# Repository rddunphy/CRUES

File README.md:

# CRUES
Co-operative robotics using environmental sensors

## Directory structure

* `docs`: Documentation, including PDF of final report
  * `docs/interim`: Interim report LaTeX root
  * `docs/final`: Final report LaTeX root
  * `docs/img`: Image root for reports
* `wiring`: Wiring diagrams, PCB files
* `rviz`: Rviz configuration files for visualising odemetry and mapping data
* `crues_pi`: ROS nodes and Python code
  * `crues_pi/ros_pkgs`: ROS packages to be added to catkin workspace
  * `crues_pi/crues`: Scripts used for testing and debugging
  * `crues_pi/config`: Configuration files for individual robots
       (Deploy script copies correct file to each RPi)
  * `crues_pi/crues_deploy`: Script for deploying code to RPis
  * `crues_pi/crues_run`: Script for running Roomba code on RPis

## Deploying and running code

* Turn on robots
* Connect to `CruesNet` ad-hoc WiFi network
* Add `crues_pi/crues_deploy` and `crues_pi/crues_run` to PATH
* Run `crues_deploy [ROBOTS]` to deploy code, with `[ROBOTS]` replaced by any combination of `blinky`, `inky` and `clyde`
* Run `crues_run [ROBOTS]` to run the `roomba.launch` ROS launch file

More details can be found in the [project Wiki](https://github.com/rddunphy/CRUES/wiki).

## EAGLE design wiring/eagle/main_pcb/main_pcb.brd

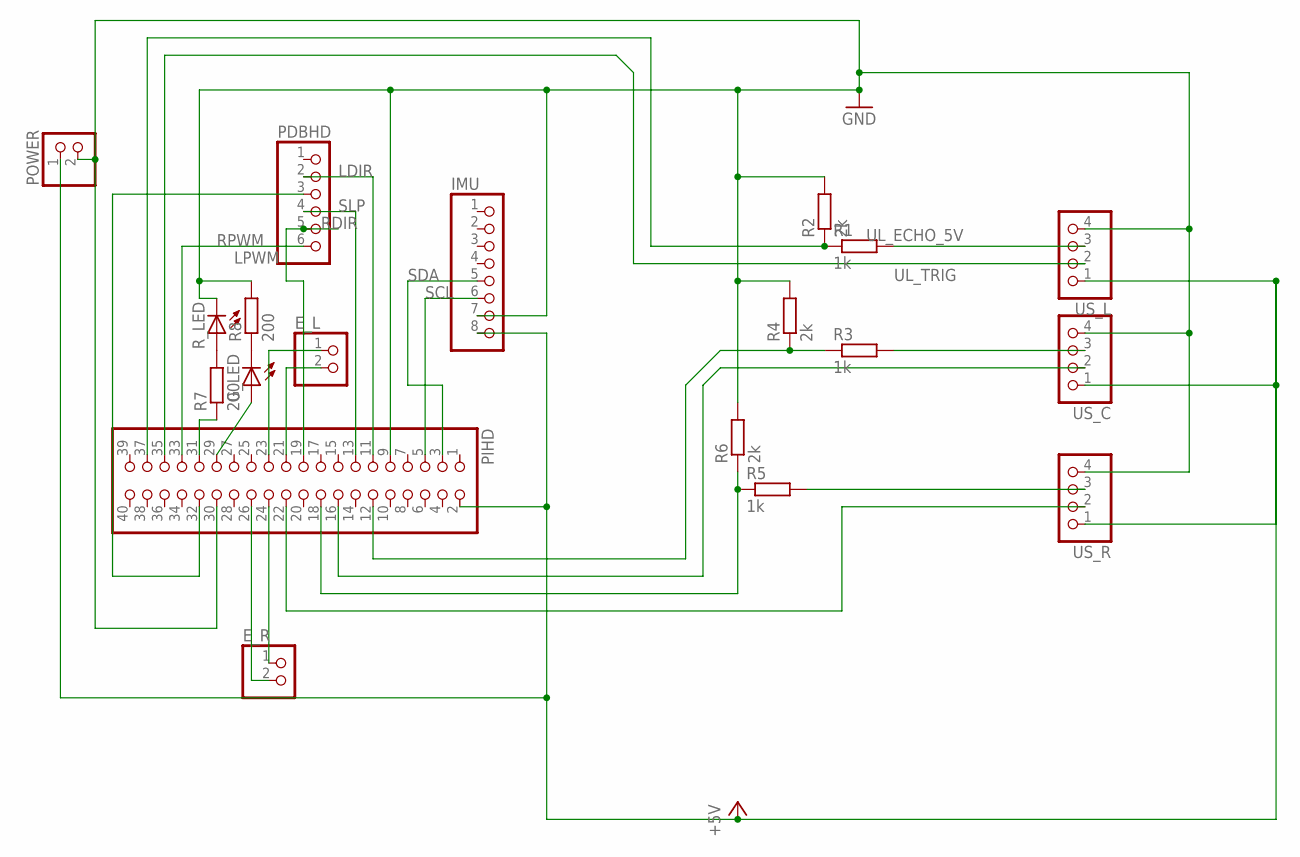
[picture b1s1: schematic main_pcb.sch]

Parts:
E_L: PINHD-1X2; 1X02
E_R: PINHD-1X2; 1X02
G_LED: LED_ELD260; LED_LD260
IMU: PINHD-1X8; 1X08
PDBHD: PINHD-1X6; 1X06
PIHD: PINHD-2X20; 2X20
POWER: PINHD-1X2; 1X02
R1, R3, R5: 1k; 0207/10
R2, R4, R6: 2k; 0207/10
R7, R8: 200; 0207/10
R_LED: LED_ELD260; LED_LD260
US_C: PINHD-1X4; 1X04
US_L: PINHD-1X4; 1X04
US_R: PINHD-1X4; 1X04

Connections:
+5V: IMU.8, PIHD.2, POWER.1, US_C.1, US_L.1, US_R.1
ER_A: E_R.1, PIHD.24
ER_B: E_R.2, PIHD.26
GND: IMU.7, PIHD.9, PIHD.30, POWER.2, R2.2, R4.2, R6.2, R8.2, R_LED.K (C), US_C.4, US_L.4, US_R.4
LDIR: PDBHD.2, PIHD.11
LED_G: G_LED.A, PIHD.29
LED_R: PIHD.31, R7.1
LPWM: PDBHD.3, PIHD.32
unnamed: E_L.2, PIHD.21
unnamed: E_L.1, PIHD.23
unnamed: R7.2, R_LED.A
unnamed: G_LED.K (C), R8.1
RDIR: PDBHD.5, PIHD.19
RPWM: PDBHD.6, PIHD.33
SCL: IMU.6, PIHD.5
SDA: IMU.5, PIHD.3
SLP: PDBHD.4, PIHD.13
UC_ECHO: PIHD.12, R3.1, R4.1
UC_ECHO_5V: R3.2, US_C.3
UC_TRIG: PIHD.16, US_C.2
UL_ECHO: PIHD.37, R1.1, R2.1
UL_ECHO_5V: R1.2, US_L.3
UL_TRIG: PIHD.35, US_L.2
UR_ECHO: PIHD.18, R5.1, R6.1
UR_ECHO_5V: R5.2, US_R.3
UR_TRIG: PIHD.22, US_R.2

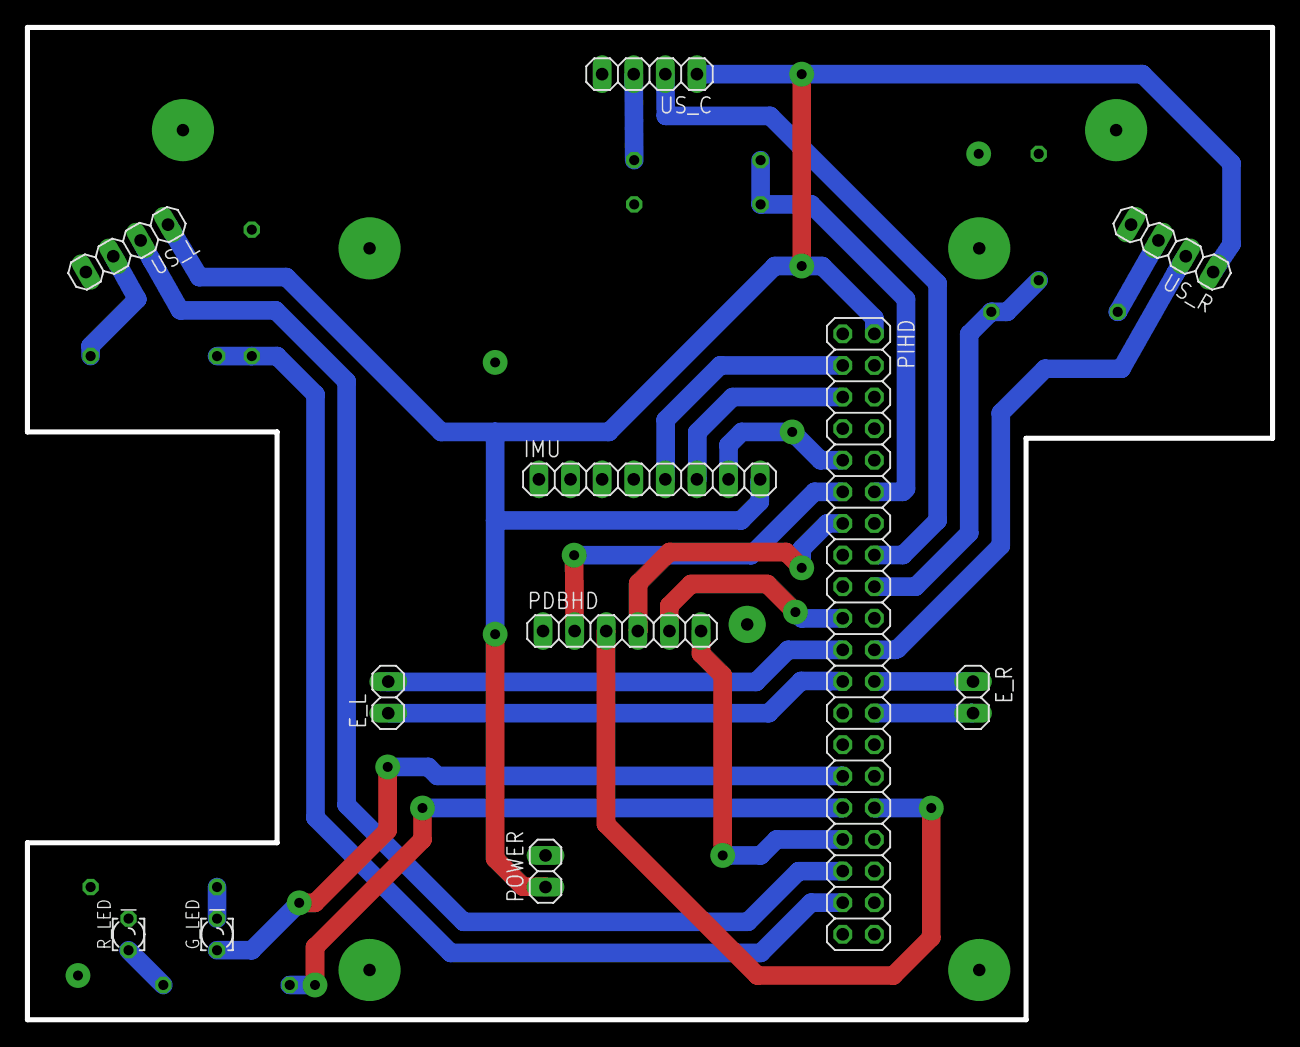
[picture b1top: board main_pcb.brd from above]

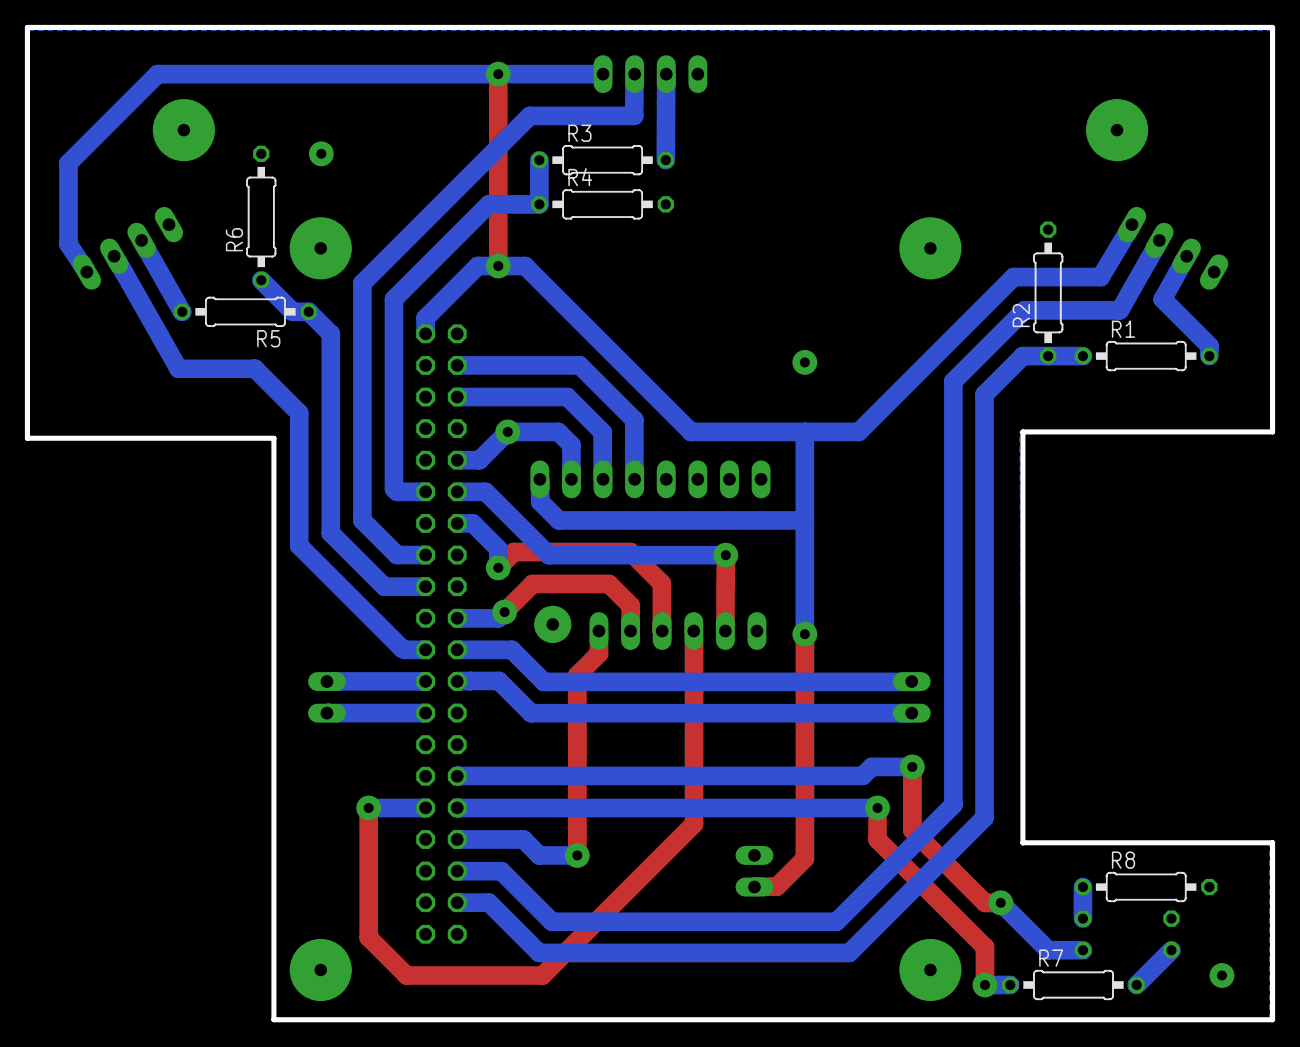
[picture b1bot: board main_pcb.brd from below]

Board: 2 copper layers, 100.1 x 79.8 mm, 19 parts (8 on the bottom side), 26 nets.

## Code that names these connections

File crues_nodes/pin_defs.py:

#!/usr/bin/env python3
"""Pin definitions for Raspberry Pi GPIO."""

# Ultrasonic sensors
UL_TRIG = 38
UL_ECHO = 40
UC_TRIG = 37
UC_ECHO = 35
UR_TRIG = 31
UR_ECHO = 29

# IMU serial pins
IMU_SCL = 5
IMU_SDA = 3

# Encoder outputs
EL_A = 22
EL_B = 18
ER_A = 13
ER_B = 11

# Motor control pins
ML_DIR = 12
ML_PWM = 32
MR_DIR = 7
MR_PWM = 33
M_SLP = 16

# LED indicators
LED_RED = 36
LED_GREEN = 28


def print_config():
    print("Ultrasonic")
    print("UL_TRIG: {}".format(UL_TRIG))
    print("UL_ECHO: {}".format(UL_ECHO))
    print("UC_TRIG: {}".format(UC_TRIG))
    print("UC_ECHO: {}".format(UC_ECHO))
    print("UR_TRIG: {}".format(UR_TRIG))
    print("UR_ECHO: {}".format(UR_ECHO))
    print()
    print("IMU")
    print("IMU_SCL: {}".format(IMU_SCL))
    print("IMU_SDA: {}".format(IMU_SDA))
    print()
    print("Encoders")
    print("EL_A: {}".format(EL_A))
    print("EL_B: {}".format(EL_B))
    print("ER_A: {}".format(ER_A))
    print("ER_B: {}".format(ER_B))
    print()
    print("Motor control")
    print("ML_DIR: {}".format(ML_DIR))
    print("ML_PWM: {}".format(ML_PWM))
    print("MR_DIR: {}".format(MR_DIR))
    print("MR_PWM: {}".format(MR_PWM))
    print("M_SLP: {}".format(M_SLP))
    print()
    print("LEDs")
    print("LED_RED: {}".format(LED_RED))
    print("LED_GREEN: {}".format(LED_GREEN))


if __name__ == '__main__':
    print_config()

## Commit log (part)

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2019-03-31 Fix concurrent.futures requirement
2019-03-31 Refactor encoder node as class
2019-03-31 Refactor ultrasonic node as class.
2019-03-31 proof reading
2019-04-01 Matt report (#39)
    * Saving files before refreshing line endings
    * git ignore upddate
    * i forget but its hoometime
    * more electrical stuff
    * added listing to imports, electrical stuff minor change in 4
    * ultrasonic software and some error fixing
2019-04-01 Kyle report (#43)
    * kfj
    * Proof read slam and updated
    * Added docs/images from abstract, group overview and posters
2019-04-01 Peter report (#45)
    * Attempt to commit docs changes
    * Refactored final doc
    * Project management report stuff
    * A little bit of pm
    * Mech doc
    * Add gitattributes file to protect against windows line endings
2019-04-01 Fetch rosbag files in deploy script.
2019-04-01 added vision in
2019-04-01 dleeted drive node
2019-04-01 Fix timezone problem
2019-04-01 No significant changes
2019-04-01 Update CMakeLists.txt
    Remove merge conflict
2019-04-01 Chassis mech changes
2019-04-01 Add IMU to robot.launch
2019-04-01 Make deploy script compatible with Andrew's weird laptop
2019-04-01 rossed the vision
2019-04-01 Consultations
2019-04-01 Gantt chart changes
2019-04-01 added code to read picam
2019-04-01 Matt report (#59)
    * Saving files before refreshing line endings
    * git ignore upddate
    * i forget but its hoometime
    * more electrical stuff
    * added listing to imports, electrical stuff minor change in 4
    * ultrasonic software and some error fixing
2019-04-01 Add rviz config file
2019-04-01 Minor fixes for EKF - main part still doesn't work
2019-04-01 Don't add Rosbag output files
2019-04-01 added pcb pic
2019-04-01 Report matt (#74)
    * added vision in
    * dleeted drive node
    * rossed the vision
    * Altered vision_node.py and package structure to allow building and running, still doesn't work
    * added code to read picam
    * tidied electronics section
2019-04-02 Add null launcher, which launches a control node that does nothing.
2019-04-02 Rename some topics for consistency, and disable IMU EKF node, as this seems to mess things up.
2019-04-02 Update topic names in rviz config
2019-04-02 Wrote the ROS background section with added references
2019-04-02 Kyle report (#75)
    * kfj
    * Proof read slam and updated
    * Added docs/images from abstract, group overview and posters
    * LE
    * Wrote the ROS background section with added references
2019-04-02 Added shortest path stuff
2019-04-02 PM section ready for review
2019-04-02 Fixed bugs and found Blinky
2019-04-02 Removed rosbag files
2019-04-02 Added up to date comms?
2019-04-02 AI and Rate control
2019-04-02 Check if robot is in view before sending
2019-04-02 Make server node class
2019-04-03 Here we go
2019-04-03 Add rospy rate to client
2019-04-03 First time, every time
2019-04-03 Made us_node more threaded
2019-04-03 Removed transform from diff_tf
2019-04-03 Add polygon controller that tries to go in a rectangle, and startup delay to avoid odometry offset.
2019-04-03 Minor changes
2019-04-03 Minor changes based on Peter's feedback
2019-04-03 Remove the excess PID stuff that came in from a previous merge
2019-04-03 Dumped US output to usdumps file
2019-04-03 Pete might be an idiot
2019-04-03 Calculated averages and put in output.txt
2019-04-03 Add Gmapping and LaserScan message
2019-04-04 Review of Project Management
2019-04-04 Need the EKF because that broadcasts the odom->baselink tf
2019-04-04 Add SLAM parameters
2019-04-04 Add screenshots
2019-04-05 Add ultrasonic diagram
2019-04-05 added recording functionality
2019-04-05 Remove accidental spacing
2019-04-05 Add path controller
2019-04-05 video improvements
2019-04-05 Start on software comms
2019-04-05 Software changes
2019-04-05 Finished Comms Design
2019-04-06 backround review
2019-04-06 More testing
2019-04-06 Testing with new lines this time
2019-04-06 Forgot to build
2019-04-06 General eval section started?
2019-04-06 Ignore rosbag directory in Git
2019-04-06 Create graph of ultrasonic response
2019-04-06 Add response to ultrasonic code
2019-04-06 Export graphs as images
2019-04-06 Add commands for setting velocity, pausing, and exiting to path controller
2019-04-06 More comms software
2019-04-06 File paths are case-sensitive
2019-04-07 Added Comms testing
2019-04-07 Start work on implementation section
2019-04-08 changes from 5/4
2019-04-08 Added changes based on Matt's susggestions
2019-04-08 Updated background for lines and other stuff
2019-04-08 Apply suggestions from code review
2019-04-08 Computer vision draft
2019-04-08 Computer vision added goal
2019-04-08 More eval
2019-04-08 Fix online references
2019-04-08 Python version subsection
2019-04-08 Minor background changes
2019-04-08 Changed paragraphs to lines
2019-04-08 Changes from Andrew's feedback
2019-04-08 Think it's fixed
2019-04-08 initial review
2019-04-08 Changes to parameters for Gmapping
2019-04-08 Move launch files to launch directories, and make ultrasonic return range in metres
2019-04-08 Refactor IMU node as class
2019-04-08 Don't need AI package at this rate
2019-04-08 Use robots.yaml for IP addresses
2019-04-08 Move config files to crues_control package
    Robot-specific config (e.g. pin definitions) in parameterised files in config directory - the correct file is selected by deploy.sh
2019-04-08 Don't need setup script anymore
2019-04-08 Requirements might still be useful, though.
2019-04-08 Publish to motor_sleep
2019-04-09 Fix minor bugs
2019-04-09 Tweak slam parameters and ignor comments in path files
2019-04-09 Update map scanner more frequently
2019-04-09 Add pinout for inky
2019-04-10 Add IMU rosbag for IMU video creation
2019-04-10 Add rviz config for IMU output
2019-04-10 Add table of pin definitions
2019-04-10 Uh oh spaghetti os
2019-04-10 review of intro
2019-04-10 A line
2019-04-10 Pin defs for clyde
2019-04-10 Update pin def table
2019-04-11 started IMU softy stuff
2019-04-11 Skim-through for getting issues together
2019-04-11 IMU image and code
2019-04-11 Requested Changes
2019-04-11 References places
2019-04-11 typos
2019-04-11 Further work??
2019-04-11 Rqeuested changes #115
2019-04-11 review
2019-04-11 References again...
2019-04-11 remove synctex temp file
2019-04-11 added loop closure stuff
2019-04-11 Because Stephen is an idiot
2019-04-11 PId complete
2019-04-11 Initial conclusion draft
2019-04-11 added citations
2019-04-11 Table problems
2019-04-11 Small change
2019-04-11 Conclusion updates from Matt's comments
2019-04-11 Wrote draft odometry section
2019-04-11 Added to Appendix A
2019-04-11 moved odometry diagram
2019-04-11 More things
2019-04-11 Fix EKF parameters
2019-04-11 Add some ekf stuff
2019-04-11 Pin assignments
2019-04-11 Misc
2019-04-11 More misc changes
2019-04-11 Modified project structure to be more consistent with reality
2019-04-11 Reviewed PID software section
2019-04-11 References stuff
2019-04-11 fixed typos for kyle and build failures for david
2019-04-11 ahhhhhh
2019-04-11 Parameterise CV colours
2019-04-11 Exclude self from list of robots to detect
2019-04-12 Basic ultrasonic synchronisation
2019-04-12 Remove conflict
2019-04-12 Add in stuff Andrew destroyed
2019-04-12 Use \verb|...| for inline code
2019-04-12 Take out some swear words
2019-04-12 Reviewed and modified software overview section
2019-04-12 Formatting Introduction
2019-04-12 review of pcb pin assignment
2019-04-12 Changes to introduction
2019-04-12 Add paragraph about output scaling to PID section
2019-04-12 Small changes
2019-04-12 start
2019-04-12 CV Review
2019-04-12 Added maze diagrams
2019-04-12 Power distro issue, needs review
2019-04-12 Forgot to reload but fixed it
2019-04-12 This time
2019-04-12 Robotics and Coop robitcs background review
2019-04-12 Please don't hurt me kyle
2019-04-12 Minor change
2019-04-12 Moved rate control to implementation to mitigate lack of references
2019-04-12 Modified rate control and stuff
2019-04-12 Appendix review, needs removed will burst before Tuesday. Recommend Dr. R.D. Dunphy for appendectomy, Dr. A. Fagan to assist
2019-04-12 Added the maze 4 Real
2019-04-12 Reviewed section, added paragraph about integration
2019-04-12 Testing Review
2019-04-12 Fixing Peter's mistake
2019-04-12 Further further work
2019-04-12 Wrote draft acknowledgement section for everyone's review. Feel free to add anything
2019-04-12 Results and something is up
2019-04-12 Minor tweaks to roomba to make it run into walls less.
    Slower turn velocity helps when there are narrow passages (one cell wide), this could be increased again for the trade show perhaps.
2019-04-12 EKF fix
2019-04-12 Forgot to reload, trying to fix
2019-04-12 Added todo
2019-04-12 Maze configuration diagrams
2019-04-13 Read-through part 1
2019-04-13 Read-through part 2
2019-04-13 Background/Lit review overhaul
2019-04-13 abstract redraft
2019-04-13 Read-through part 3
2019-04-13 test review
2019-04-13 pin def check
2019-04-13 some minor changes
2019-04-13 Read-through part 5
2019-04-13 wrote high level overview of package, still to write tuning
2019-04-13 Evaluation review
2019-04-13 Software evaluation
2019-04-13 Read-through part 6
2019-04-13 Further work changes
2019-04-13 Read-through part 7
2019-04-13 Read-through part 8
2019-04-13 Read-through part 9. Got partway through background on second read-through
2019-04-13 added figure and some analysis
2019-04-14 Some proof reading changes for abstract, introduction and background
2019-04-14 Background proof-read
2019-04-14 Project management changes
2019-04-14 Mechanical review
2019-04-14 Move all code to local catkin workspace
2019-04-14 Add apt packages needed for installation
2019-04-14 Sofware review
2019-04-14 Don't mention the batteries!
2019-04-14 Further work
2019-04-14 Conclusions review
2019-04-14 Fix missing page numbers in toc
2019-04-14 Proofreading
2019-04-14 Significant work on ROS software section
2019-04-14 Got rid of todos
2019-04-14 "deal with" doesn't sound reporty.
2019-04-14 Fix IMU todo
2019-04-14 Add EKF graphs
2019-04-14 Fixed ALL the Latex warnings!
    Also added todo list to the start of the report, to make todos easy to
    find
2019-04-14 Add SLAM figures
2019-04-14 fixed a couple things
2019-04-14 Add AMCL diagram
2019-04-14 Fix dates in bibliography
2019-04-14 Fixed build error
2019-04-14 Changed some things in conclusion
2019-04-14 Review software intro
2019-04-15 Minor again
2019-04-15 Add all chapters to texwc
2019-04-15 Evaluation
2019-04-15 modules, plural
2019-04-15 Add a todo
2019-04-15 Add encoder unit test
2019-04-15 Update 06_software.tex
    minor reword
2019-04-15 Update 06_software.tex
    tsk tsk
2019-04-15 Merge
2019-04-15 Fix syntax error
2019-04-15 proof read suggestions
2019-04-15 Remove individual runtimes from results table
2019-04-15 Pickiness
2019-04-15 fixed references to Raspberry pi to RPI, unless raspberry made more sense
2019-04-15 Wrote up mapping
2019-04-15 Some small updates
2019-04-15 Structural changes
2019-04-15 Fuck you David
2019-04-15 Moved image to sort large whitespace
2019-04-15 Remove todo
2019-04-15 added analysis and graph to ultrasonic
2019-04-15 Read-through Part 10
2019-04-15 Review mainly software
2019-04-15 Finally wrote control node section.
2019-04-15 stuff
2019-04-15 Read-through Part 11
2019-04-15 Fixed refs
2019-04-15 Todo Execution
2019-04-15 Refactor 2
2019-04-15 Refactor 3
2019-04-15 Reflection
2019-04-15 diff drive additions for review
2019-04-15 Testing proof read
2019-04-15 E and M review
2019-04-15 ultrasonic synchronisation
2019-04-15 fixed imu code and discussion
2019-04-15 Remove double words
2019-04-15 Changed bracket issue
2019-04-15 remove 'see sections'
2019-04-15 Sorted co-operative and coordinate constitency
2019-04-15 Software Testing picture sorting
2019-04-15 More minor changes
2019-04-15 Something, too tired
2019-04-16 Wall follower
2019-04-16 Minor changes 2
2019-04-18 Tweaks to velocities for trade show
